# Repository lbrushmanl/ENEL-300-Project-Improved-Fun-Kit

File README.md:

# ENEL-300-Project-Improved-Fun-Kit

For more info on the project a copy of our report is in the repository.

The main Board

Pin Quick Reference

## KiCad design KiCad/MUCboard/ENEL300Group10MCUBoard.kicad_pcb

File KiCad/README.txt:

There are 3 boards for manufacturing each is in its own folder

Names of these boards are:
MCUboard
Gamesboard
Audioboard

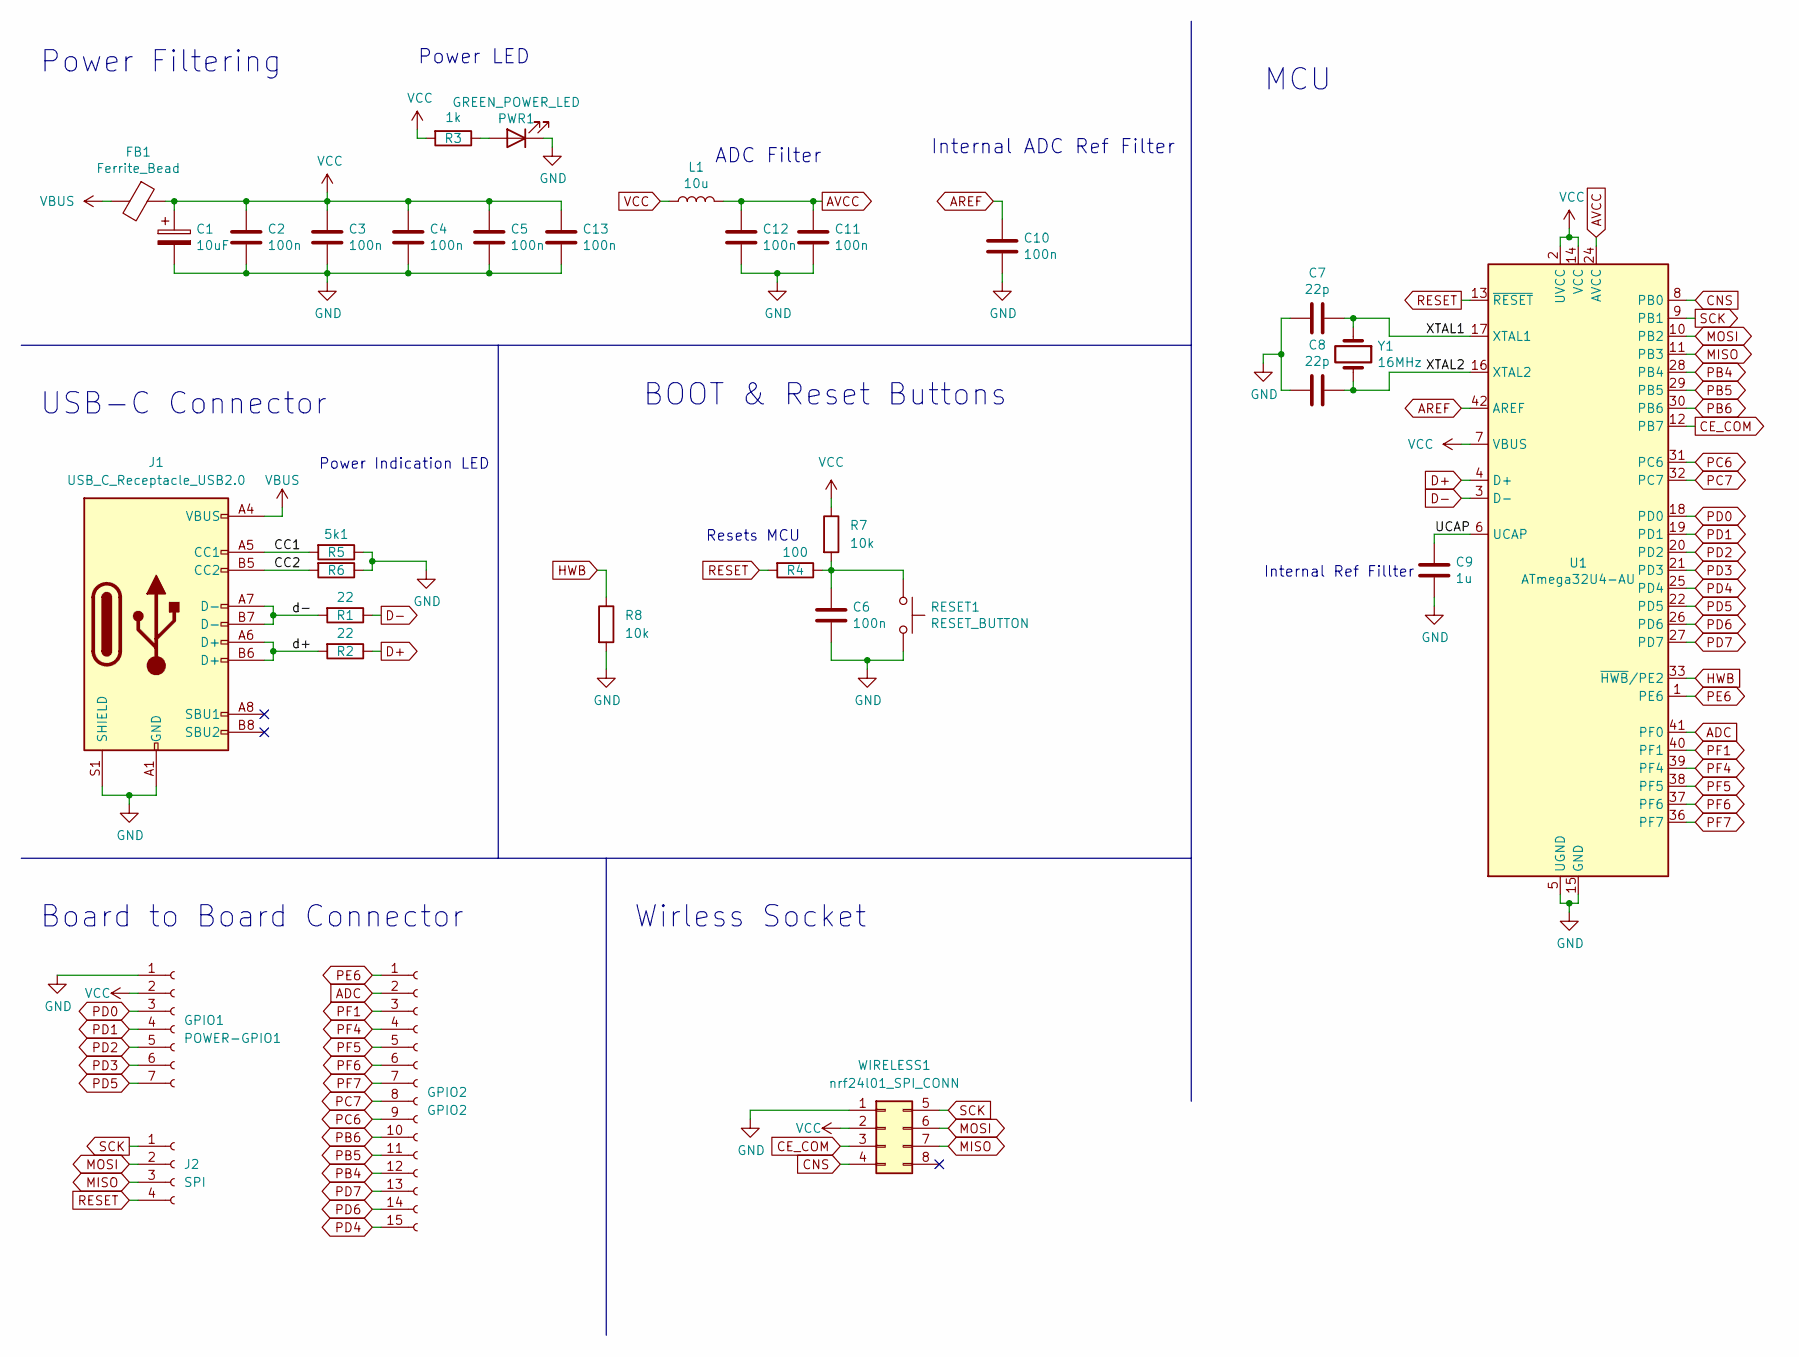
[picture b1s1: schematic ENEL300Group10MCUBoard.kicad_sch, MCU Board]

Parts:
C1: 10uF; C_0805_2012Metric_Pad1.18x1.45mm_HandSolder
C2, C3, C4, C5, C6, C10, C11, C12, C13: 100n; C_0603_1608Metric_Pad1.08x0.95mm_HandSolder
C7, C8: 22p; C_0603_1608Metric_Pad1.08x0.95mm_HandSolder
C9: 1u; C_0603_1608Metric_Pad1.08x0.95mm_HandSolder
FB1: Ferrite_Bead; L_0805_2012Metric_Pad1.15x1.40mm_HandSolder
GPIO1: POWER-GPIO1; PinSocket_1x07_P2.54mm_Vertical
GPIO2: GPIO2; PinSocket_1x15_P2.54mm_Vertical
J1: USB_C_Receptacle_USB2.0; GCT_USB4105-GF-A
J2: SPI; PinSocket_1x04_P2.54mm_Vertical
L1: 10u; L_0805_2012Metric_Pad1.15x1.40mm_HandSolder
PWR1: GREEN_POWER_LED; LED_1206_3216Metric_ReverseMount_Hole1.8x2.4mm
R1, R2: 22; R_0603_1608Metric_Pad0.98x0.95mm_HandSolder
R3: 1k; R_0603_1608Metric_Pad0.98x0.95mm_HandSolder
R4: 100; R_Axial_DIN0207_L6.3mm_D2.5mm_P15.24mm_Horizontal
R5, R6: 5k1; R_0603_1608Metric_Pad0.98x0.95mm_HandSolder
R7, R8: 10k; R_0603_1608Metric_Pad0.98x0.95mm_HandSolder
RESET1: RESET_BUTTON; SW_Tactile_SPST_Angled_PTS645Vx31-2LFS
U1: ATmega32U4-AU; TQFP-44_10x10mm_P0.8mm
WIRELESS1: nrf24l01_SPI_CONN; PinSocket_2x04_P2.54mm_Vertical
Y1: 16MHz; Crystal_HC18-U_Vertical

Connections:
/CC1: J1.A5 (CC1), R5.2
/CC2: J1.B5 (CC2), R6.2
/UCAP: C9.1, U1.6 (UCAP)
/XTAL1: C7.1, U1.17 (XTAL1), Y1.1
/XTAL2: C8.1, U1.16 (XTAL2), Y1.2
/d+: J1.A6 (D+), J1.B6 (D+), R2.2
/d-: J1.A7 (D-), J1.B7 (D-), R1.2
ADC: GPIO2.2, U1.41 (PF0)
AREF: C10.1, U1.42 (AREF)
AVCC: C11.1, C12.1, L1.2, U1.24 (AVCC), U1.44 (AVCC)
CE_COM: U1.12 (PB7), WIRELESS1.3
CNS: U1.8 (PB0), WIRELESS1.4
D+: R2.1, U1.4 (D+)
D-: R1.1, U1.3 (D-)
GND: C1.2, C2.2, C3.2, C4.2, C5.2, C6.2, C7.2, C8.2, C9.2, C10.2, C11.2, C12.2, C13.2, GPIO1.1, J1.A1 (GND), J1.A12 (GND), J1.B1 (GND), J1.B12 (GND), J1.S1 (SHIELD), PWR1.1 (K), R5.1, R6.1, R8.2, RESET1.2, U1.5 (UGND), U1.15 (GND), U1.23 (GND), U1.35 (GND), U1.43 (GND), WIRELESS1.1
HWB: R8.1, U1.33 (~HWB/PE2)
MISO: J2.3, U1.11 (PB3), WIRELESS1.7
MOSI: J2.2, U1.10 (PB2), WIRELESS1.6
unnamed: C6.1, R4.1, R7.2, RESET1.1
unnamed: PWR1.2 (A), R3.1
PB4: GPIO2.12, U1.28 (PB4)
PB5: GPIO2.11, U1.29 (PB5)
PB6: GPIO2.10, U1.30 (PB6)
PC6: GPIO2.9, U1.31 (PC6)
PC7: GPIO2.8, U1.32 (PC7)
PD0: GPIO1.3, U1.18 (PD0)
PD1: GPIO1.4, U1.19 (PD1)
PD2: GPIO1.5, U1.20 (PD2)
PD3: GPIO1.6, U1.21 (PD3)
PD4: GPIO2.15, U1.25 (PD4)
PD5: GPIO1.7, U1.22 (PD5)
PD6: GPIO2.14, U1.26 (PD6)
PD7: GPIO2.13, U1.27 (PD7)
PE6: GPIO2.1, U1.1 (PE6)
PF1: GPIO2.3, U1.40 (PF1)
PF4: GPIO2.4, U1.39 (PF4)
PF5: GPIO2.5, U1.38 (PF5)
PF6: GPIO2.6, U1.37 (PF6)
PF7: GPIO2.7, U1.36 (PF7)
RESET: J2.4, R4.2, U1.13 (~RESET)
SCK: J2.1, U1.9 (PB1), WIRELESS1.5
VBUS: FB1.2, J1.A4 (VBUS), J1.A9 (VBUS), J1.B4 (VBUS), J1.B9 (VBUS)
VCC: C1.1, C2.1, C3.1, C4.1, C5.1, C13.1, FB1.1, GPIO1.2, L1.1, R3.2, R7.1, U1.2 (UVCC), U1.7 (VBUS), U1.14 (VCC), U1.34 (VCC), WIRELESS1.2

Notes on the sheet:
Resets MCU
Board to Board Connector
Power Filtering
Power LED
ADC Filter
USB-C Connector
Wirless Socket
Power Indication LED
Internal ADC Ref Filter
MCU
BOOT & Reset Buttons
Internal Ref Fillter

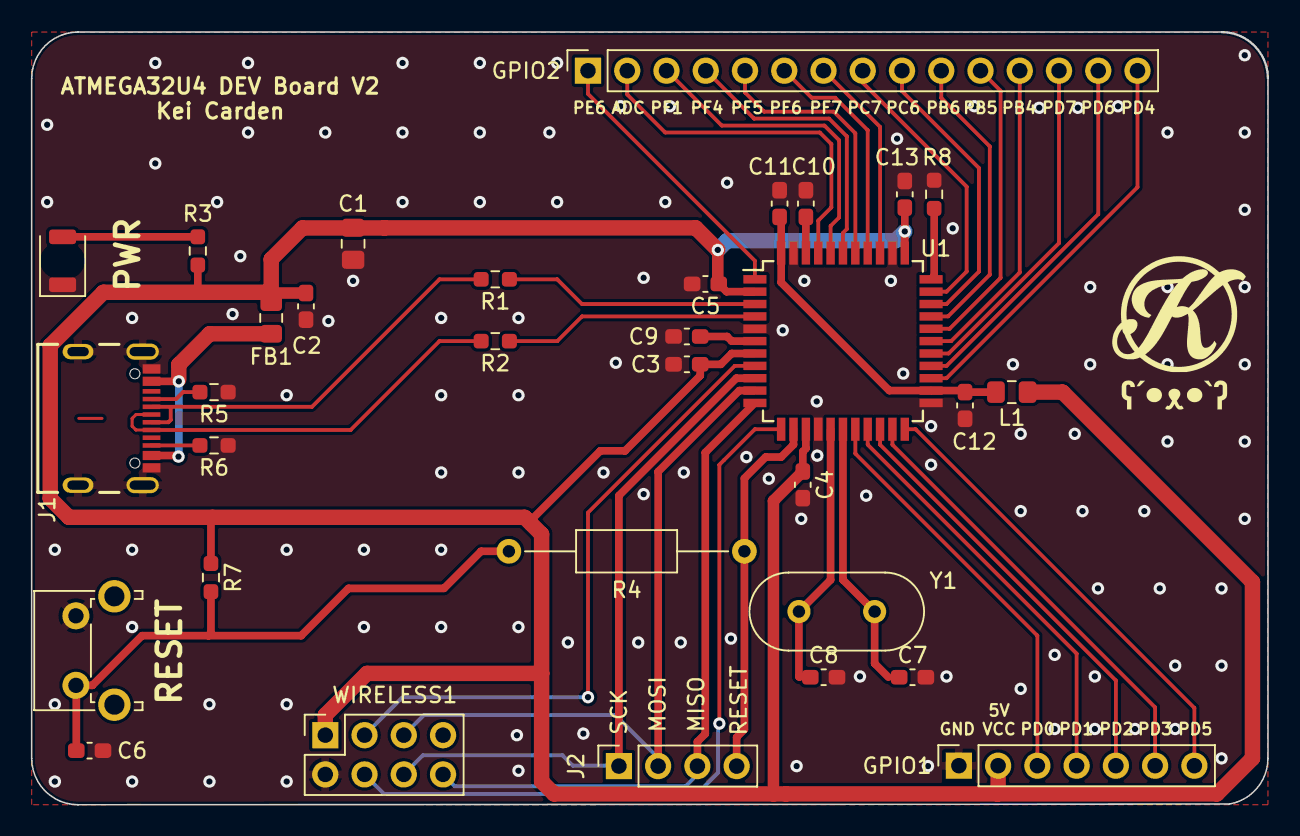
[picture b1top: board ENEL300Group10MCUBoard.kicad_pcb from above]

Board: 2 copper layers, 80.0 x 50.0 mm, 32 parts (0 on the bottom side), 43 nets.

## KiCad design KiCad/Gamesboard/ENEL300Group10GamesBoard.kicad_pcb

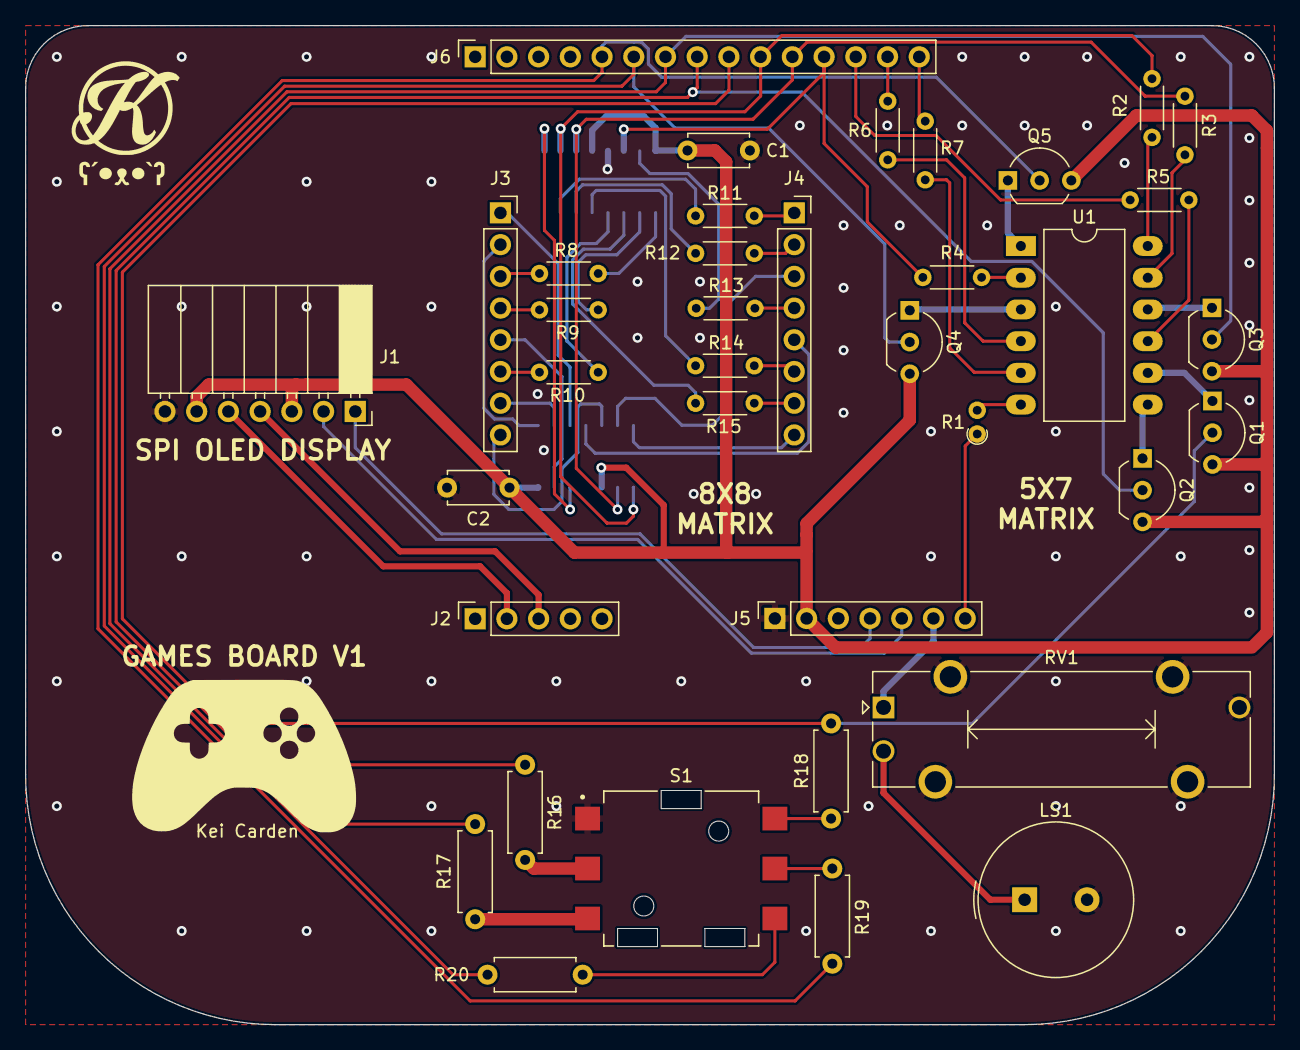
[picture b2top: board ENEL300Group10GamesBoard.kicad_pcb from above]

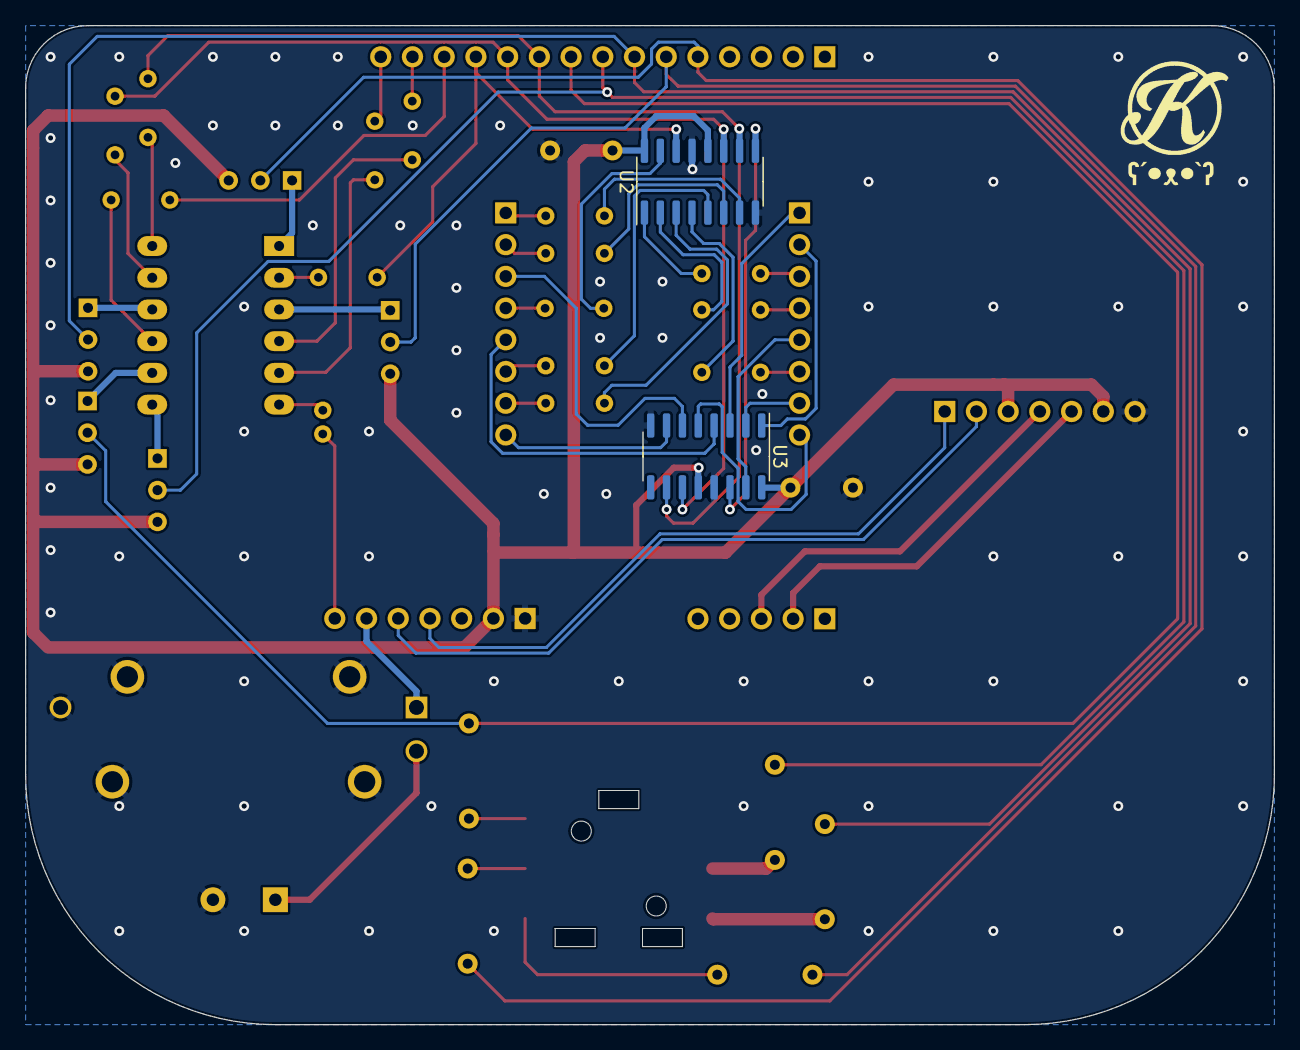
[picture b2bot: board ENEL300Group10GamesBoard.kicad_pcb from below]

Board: 2 copper layers, 100.0 x 80.0 mm, 39 parts (2 on the bottom side), 62 nets.

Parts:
C1, C2: 100n; C_Disc_D4.7mm_W2.5mm_P5.00mm
J1: OLED-CONN; PinSocket_1x07_P2.54mm_Horizontal
J2: Conn_01x05_Female; PinSocket_1x05_P2.54mm_Vertical
J3: 8x8-MATRIX-LEFT-CONN; PinSocket_1x08_P2.54mm_Vertical
J4: 8x8-MATRIX-RIGHT-CONN; PinSocket_1x08_P2.54mm_Vertical
J5: Conn_01x07_Female; PinSocket_1x07_P2.54mm_Vertical
J6: RIGHT-BOARD-CONN; PinSocket_1x15_P2.54mm_Vertical
LS1: Speaker; Buzzer_TDK_PS1240P02BT_D12.2mm_H6.5mm
Q1, Q2, Q3, Q4, Q5: 2N7000; TO-92_Inline_Wide
R1: 100; R_Axial_DIN0204_L3.6mm_D1.6mm_P1.90mm_Vertical
R2, R3, R4, R5, R6, R7: 100; R_Axial_DIN0204_L3.2mm_D1.7mm_P5.08MM_Horizontal
R8, R9, R10, R11, R12, R13, R14, R15: 220; R_Axial_DIN0204_L3.2mm_D1.7mm_P5.08MM_Horizontal
R16, R17, R18, R19, R20: 2k2; R_Axial_DIN0207_L6.3mm_D2.5mm_P7.62mm_Horizontal
RV1: R_Potentiometer; Potentiometer_Bourns_PTA1543_Single_Slide
S1: JS5208; SW_JS5208
U1: TA07_LED_M_ATRIX; DIP-12_W10.16mm_LongPads
U2, U3: 74HC595; SOIC-16_3.9x9.9mm_P1.27mm

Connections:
/SW1: R16.2, S1.2
/SW2: R17.2, S1.3
/SW3: R18.1, S1.4
/SW4: R19.1, S1.5
/SW5: R20.1, S1.6
A0: J1.2, J5.5
COL1: J6.5, Q5.2 (G), R19.2
COL2: J6.6, Q4.2 (G), R20.2
COL3: J6.7, Q3.2 (G), R17.1
COL4: J6.8, Q2.2 (G), R16.1
COL5: J6.9, Q1.2 (G), R18.2
CS: J1.1, J5.4
DATA: J6.12, R4.2, U2.14 (SER)
GND: C1.1, C2.1, J1.7, J5.1, LS1.2, RV1.3, S1.1, U2.8 (GND), U2.13 (~OE), U3.8 (GND), U3.13 (~OE)
Latch: J6.10, R2.2, U2.10 (~SRCLR), U3.10 (~SRCLR)
MOSI: J1.4, J2.3
MX-COL1: J3.5, U3.15 (QA)
MX-COL2: J3.2, U3.1 (QB)
MX-COL3: J3.7, U3.2 (QC)
MX-COL4: J3.1, U3.3 (QD)
MX-COL5: J4.5, U3.4 (QE)
MX-COL6: J3.8, U3.5 (QF)
MX-COL7: J4.3, U3.6 (QG)
MX-COL8: J4.8, U3.7 (QH)
MX-ROW1: R13.1, U2.15 (QA)
MX-ROW2: R8.1, U2.1 (QB)
MX-ROW3: R9.1, U2.2 (QC)
MX-ROW4: R15.1, U2.3 (QD)
MX-ROW5: R10.1, U2.4 (QE)
MX-ROW6: R14.1, U2.5 (QF)
MX-ROW7: R12.1, U2.6 (QG)
MX-ROW8: R11.1, U2.7 (QH)
unnamed: J3.3, R8.2
unnamed: J3.4, R9.2
unnamed: J3.6, R10.2
unnamed: J4.1, R11.2
unnamed: J4.2, R12.2
unnamed: J4.4, R13.2
unnamed: J4.6, R14.2
unnamed: J4.7, R15.2
unnamed: LS1.1, RV1.2
unnamed: Q1.1 (S), U1.8 (C5)
unnamed: Q2.1 (S), U1.7 (C4)
unnamed: Q3.1 (S), U1.10 (C3)
unnamed: Q4.1 (S), U1.3 (C2)
unnamed: Q5.1 (S), U1.1 (C1)
unnamed: R1.2, U1.6 (R7)
unnamed: R2.1, U1.12 (R1)
unnamed: R3.1, U1.11 (R2)
unnamed: R4.1, U1.2 (R3)
unnamed: R5.1, U1.9 (R4)
unnamed: R6.1, U1.4 (R5)
unnamed: R7.1, U1.5 (R6)
ROW2: J6.11, R3.2, U2.11 (SRCLK), U3.11 (SRCLK)
ROW4: J6.13, R5.2
ROW5: J6.14, R6.2
ROW6: J6.15, R7.2
ROW7: J5.7, R1.1
SCK: J1.5, J2.2
SER2: U2.9 (QH'), U3.14 (SER)
Sound: J5.6, RV1.1
VCC: C1.2, C2.2, J1.3, J1.6, J5.2, Q1.3 (D), Q2.3 (D), Q3.3 (D), Q4.3 (D), Q5.3 (D), U2.12 (RCLK), U2.16 (VCC), U3.12 (RCLK), U3.16 (VCC)

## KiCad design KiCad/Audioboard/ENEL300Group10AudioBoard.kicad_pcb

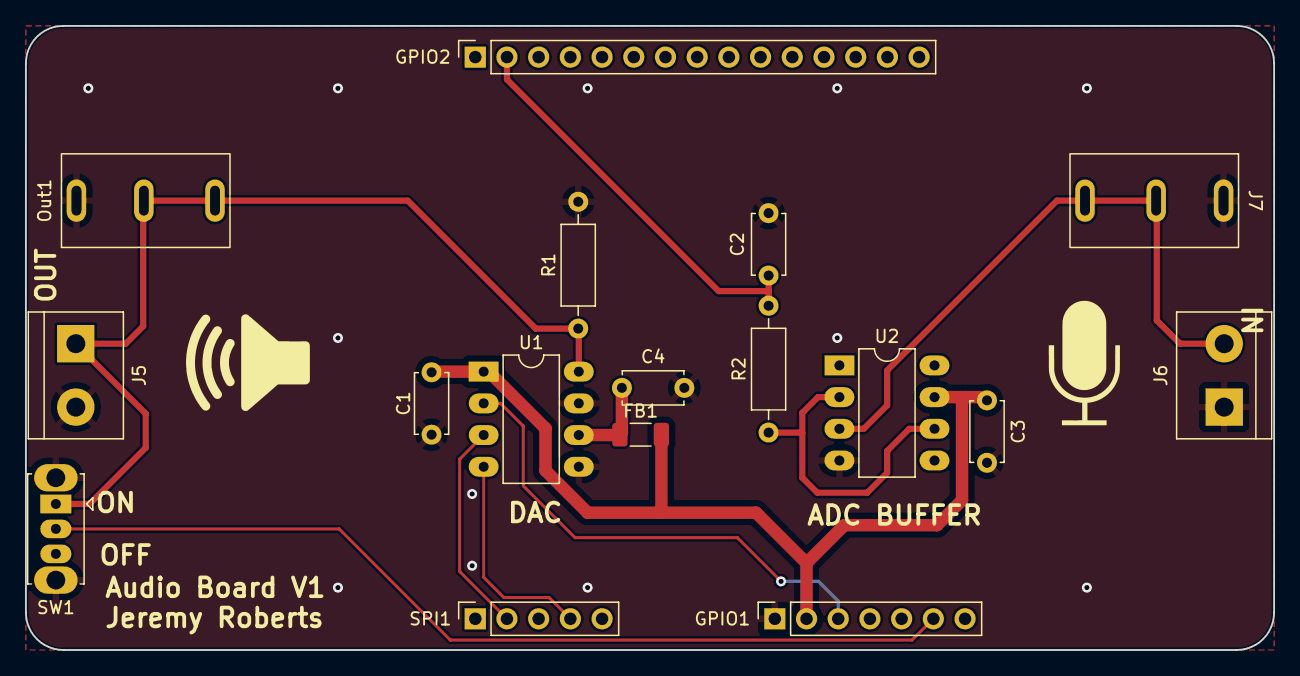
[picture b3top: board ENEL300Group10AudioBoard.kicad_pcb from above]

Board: 2 copper layers, 100.0 x 50.0 mm, 17 parts (0 on the bottom side), 11 nets.

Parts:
C1, C2, C3, C4: 100n; C_Disc_D4.7mm_W2.5mm_P5.00mm
FB1: FerriteBead; L_1206_3216Metric_Pad1.22x1.90mm_HandSolder
GPIO1: Conn_01x07_Female; PinSocket_1x07_P2.54mm_Vertical
GPIO2: GPIO; PinSocket_1x15_P2.54mm_Vertical
J5, J6: Screw_Terminal_01x02; TerminalBlock_bornier-2_P5.08mm
J7: AudioJack2; G-1360
Out1: AudioJack2; G-1360
R1: R; R_Axial_DIN0207_L6.3mm_D2.5mm_P10.16mm_Horizontal
R2: 15; R_Axial_DIN0207_L6.3mm_D2.5mm_P10.16mm_Horizontal
SPI1: Conn_01x05_Female; PinSocket_1x05_P2.54mm_Vertical
SW1: SW_SPST; SW_Slide_1P2T_CK_OS102011MS2Q
U1: MCP4921; DIP-8_W7.62mm_LongPads
U2: TL071; DIP-8_W7.62mm_LongPads

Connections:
ADC: C2.1, GPIO2.2, R2.2
CS#: GPIO1.3, U1.2 (~CS)
GND: C1.2, C2.2, C3.2, C4.2, GPIO1.1, J5.2, J6.1, J7.S, Out1.S, R1.2, SW1.GND, U1.5 (~LDAC), U1.7 (Vss), U2.4 (V-)
unnamed: J5.1, Out1.T, R1.1, SW1.1 (A), U1.8 (Vout)
unnamed: J6.2, J7.T, U2.3 (+)
unnamed: R2.1, U2.2 (-), U2.6
SCK: SPI1.2, U1.3 (SCK)
SDO: SPI1.4, U1.4 (SDI)
Speaker: GPIO1.6, SW1.2 (B)
VCC: C1.1, C3.1, FB1.2, GPIO1.2, U1.1 (Vdd), U2.7 (V+)
VREF: C4.1, FB1.1, U1.6 (Vref)

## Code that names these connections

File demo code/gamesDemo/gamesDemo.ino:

int currentRow = 1;
int currentCol = 1;


#define rightMove something
#define leftMove something
#define upMove something
#define downMove something


void setup()  {   
  // put  your setup  code  here, to  run once:   
  pinMode(A2,  OUTPUT);   
  pinMode(A1,  OUTPUT);  //Col2 
  pinMode(A0,  OUTPUT);  //Col3   
  pinMode(13,  OUTPUT); //Col4  
  pinMode(5,  OUTPUT); //Col5 
  pinMode(10,  OUTPUT); //Row1  
  pinMode(9,  OUTPUT); //Row2  
  pinMode(8,  OUTPUT);  
  pinMode(6,  OUTPUT); 
  pinMode(12,  OUTPUT); 
  pinMode(4,  OUTPUT); 
  pinMode(TX, OUTPUT);

  pinMode(rightMove, INPUT);
  pinMode(leftMove, INPUT);
  pinMode(upMove, INPUT);
  pinMode(downMove, INPUT);
  } 
  
  void loop()  {   
    // put  your main code  here, to  run repeatedly:   

    if (rightMove == HIGH) {
      if (currentRow >= 7) {
        currentRow = 1;
      } else {
        currentRow += 1;
      }
      
    } else if (leftMove == HIGH) {
      if (currentRow <= 1) {
        currentRow = 7;
      } else {
        currentRow -= 1;
      }
      
    } else if (upMove == HIGH) {
      if (currentCol >= 5) {
        currentRow = 1;
      } else {
        currentRow += 1;
      }
      
    } else if (downMove == HIGH) {
      if (currentRow >= 7) {
        currentRow = 1;
      } else {
        currentRow += 1;
      }
    }

    if (currentRow == 1) {
      digitalWrite(A2, HIGH);
      digitalWrite(A1, LOW);
      digitalWrite(A0, LOW);
      digitalWrite(13, LOW);
      digitalWrite(5, LOW);
    } else if (currentRow == 2) {
      digitalWrite(A2, LOW);
      digitalWrite(A1, HIGH);
      digitalWrite(A0, LOW);
      digitalWrite(13, LOW);
      digitalWrite(5, LOW);
    } else if (currentRow == 3) {
      digitalWrite(A2, LOW);
      digitalWrite(A1, LOW);
      digitalWrite(A0, HIGH);
      digitalWrite(13, LOW);
      digitalWrite(5, LOW);
    } else if (currentRow == 4) {
      digitalWrite(A2, LOW);
      digitalWrite(A1, LOW);
      digitalWrite(A0, LOW);
      digitalWrite(13, HIGH);
      digitalWrite(5, LOW);
    } else if (currentRow == 5) {
      digitalWrite(A2, LOW);
      digitalWrite(A1, LOW);
      digitalWrite(A0, LOW);
      digitalWrite(13, LOW);
      digitalWrite(5, HIGH);
    }

    if (currentCol == 1) {
      digitalWrite(10, LOW);
      digitalWrite(9, HIGH);
      digitalWrite(8, HIGH);
      digitalWrite(6, HIGH);
      digitalWrite(12, HIGH);
      digitalWrite(4, HIGH);
      digitalWrite(TX, HIGH);
    } else if (currentCol == 2) {
      digitalWrite(10, HIGH);
      digitalWrite(9, LOW);
      digitalWrite(8, HIGH);
      digitalWrite(6, HIGH);
      digitalWrite(12, HIGH);
      digitalWrite(4, HIGH);
      digitalWrite(TX, HIGH);
    } else if (currentCol == 3) {
      digitalWrite(10, HIGH);
      digitalWrite(9, HIGH);
      digitalWrite(8, LOW);
      digitalWrite(6, HIGH);
      digitalWrite(12, HIGH);
      digitalWrite(4, HIGH);
      digitalWrite(TX, HIGH);
    } else if (currentCol == 4) {
      digitalWrite(10, HIGH);
      digitalWrite(9, HIGH);
      digitalWrite(8, HIGH);
      digitalWrite(6, LOW);
      digitalWrite(12, HIGH);
      digitalWrite(4, HIGH);
      digitalWrite(TX, HIGH);
    } else if (currentCol == 5) {
      digitalWrite(10, HIGH);
      digitalWrite(9, HIGH);
      digitalWrite(8, HIGH);
      digitalWrite(6, HIGH);
      digitalWrite(12, LOW);
      digitalWrite(4, HIGH);
      digitalWrite(TX, HIGH);
    } else if (currentCol == 6) {
      digitalWrite(10, HIGH);
      digitalWrite(9, HIGH);
      digitalWrite(8, HIGH);
      digitalWrite(6, HIGH);
      digitalWrite(12, HIGH);
      digitalWrite(4, LOW);
      digitalWrite(TX, HIGH);
    } else if (currentCol == 7) {
      digitalWrite(10, HIGH);
      digitalWrite(9, HIGH);
      digitalWrite(8, HIGH);
      digitalWrite(6, HIGH);
      digitalWrite(12, HIGH);
      digitalWrite(4, HIGH);
      digitalWrite(TX, LOW);
    }
  }

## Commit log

2023-04-26 Adding Project
